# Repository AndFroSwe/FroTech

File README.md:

# This repo will be empried and removed

# FroTech library
Contains electrical projects that are too small to be in their own repo.

## Projects
Here, projects are listed.

### BoostBoard (WIP)
Board that can be connected to 5V and boost output to 9V or 12V. Meant
to be used in USB powered low power applications.

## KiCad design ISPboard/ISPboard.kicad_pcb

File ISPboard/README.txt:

#####################################
# README for ISPboard               #
# ###################################
# Project description:
# Board for attaching DIP28 Atmel chips
# and program and debug them over ISP.
# Also features 2 LEDs and 2 buttons that
# can be connected via jumpers to quickly test
# chip programming.
#####################################
# Revisions                         #
#####################################
Mk I
LEDS and buttons, connection for ISP.

Mk II
Added a PSU from battery and an on/off-switch.
Added pullups to buttons.

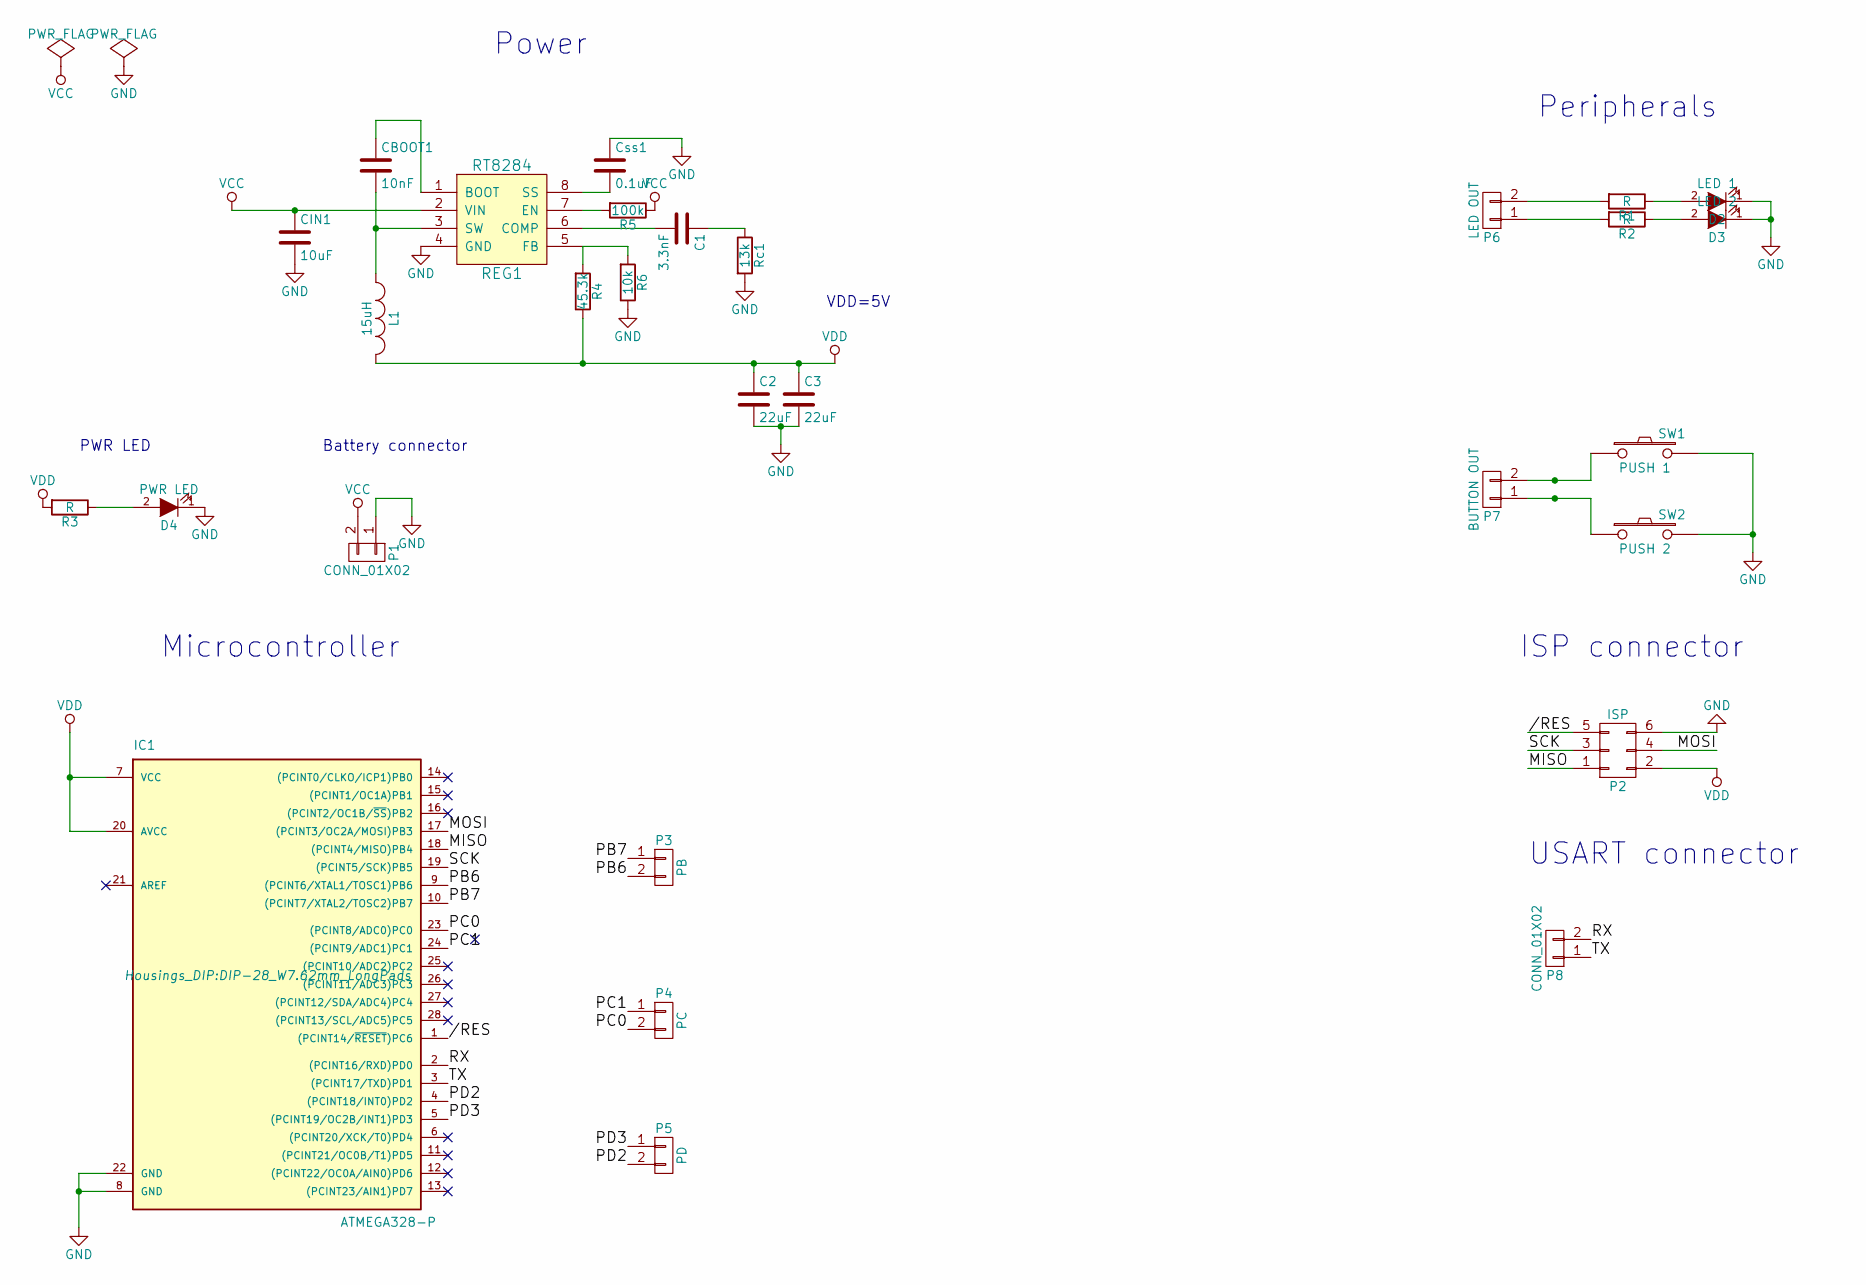
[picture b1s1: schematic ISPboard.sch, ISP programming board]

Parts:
C1: 3.3nF; C_0805_HandSoldering
C2, C3: 22uF; c_elec_4x4.5
CBOOT1: 10nF; C_0805_HandSoldering
CIN1: 10uF; c_elec_4x4.5
Css1: 0.1uF; C_0805_HandSoldering
D2: LED 1; LED-5MM
D3: LED 2; LED-5MM
D4: PWR LED; LED-5MM
IC1: ATMEGA328-P; DIP-28_W7.62mm_LongPads
L1: 15uH; Choke_SMD_Wuerth-WE-PD2-Typ-L
P1: CONN_01X02; Socket_Strip_Straight_1x02
P2: ISP; Socket_Strip_Straight_2x03
P3: PB; Molex_KK-6410-02_02x2.54mm_Straight
P4: PC; Molex_KK-6410-02_02x2.54mm_Straight
P5: PD; Molex_KK-6410-02_02x2.54mm_Straight
P6: LED OUT; Molex_KK-6410-02_02x2.54mm_Straight
P7: BUTTON OUT; Molex_KK-6410-02_02x2.54mm_Straight
P8: CONN_01X02; Molex_KK-6410-02_02x2.54mm_Straight
R1, R2, R3: R; R_1206_HandSoldering
R4: 45.3k; R_1206_HandSoldering
R5: 100k; R_1206_HandSoldering
R6: 10k; R_1206_HandSoldering
REG1: RT8284; SO-8
Rc1: 13k; R_1206_HandSoldering
SW1: PUSH 1; SW_PUSH_6mm
SW2: PUSH 2; SW_PUSH_6mm

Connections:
//RES: IC1.1 ((PCINT14/~RESET~)PC6), P2.5
/MISO: IC1.18 ((PCINT4/MISO)PB4), P2.1
/MOSI: IC1.17 ((PCINT3/OC2A/MOSI)PB3), P2.4
/PB6: IC1.9 ((PCINT6/XTAL1/TOSC1)PB6), P3.2
/PB7: IC1.10 ((PCINT7/XTAL2/TOSC2)PB7), P3.1
/PC0: IC1.23 ((PCINT8/ADC0)PC0), P4.2
/PC1: IC1.24 ((PCINT9/ADC1)PC1), P4.1
/PD2: IC1.4 ((PCINT18/INT0)PD2), P5.2
/PD3: IC1.5 ((PCINT19/OC2B/INT1)PD3), P5.1
/RX: IC1.2 ((PCINT16/RXD)PD0), P8.2
/SCK: IC1.19 ((PCINT5/SCK)PB5), P2.3
/TX: IC1.3 ((PCINT17/TXD)PD1), P8.1
GND: C2.2, C3.2, CIN1.2, Css1.1, D2.1 (K), D3.1 (K), D4.1 (K), IC1.8 (GND), IC1.22 (GND), P1.1, P2.6, R6.1, REG1.4 (GND), Rc1.2, SW1.2, SW2.2
unnamed: C1.1, Rc1.1
unnamed: C1.2, REG1.6 (COMP)
unnamed: CBOOT1.1, REG1.1 (BOOT)
unnamed: CBOOT1.2, L1.1, REG1.3 (SW)
unnamed: Css1.2, REG1.8 (SS)
unnamed: D2.2 (A), R1.1
unnamed: D3.2 (A), R2.1
unnamed: D4.2 (A), R3.1
unnamed: P6.1, R2.2
unnamed: P6.2, R1.2
unnamed: P7.1, SW2.1
unnamed: P7.2, SW1.1
unnamed: R4.2, R6.2, REG1.5 (FB)
unnamed: R5.2, REG1.7 (EN)
VCC: CIN1.1, P1.2, R5.1, REG1.2 (VIN)
VDD: C2.1, C3.1, IC1.7 (VCC), IC1.20 (AVCC), L1.2, P2.2, R3.2, R4.1

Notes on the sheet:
Microcontroller
Power
ISP connector
Peripherals
PWR LED
Battery connector
VDD=5V
USART connector

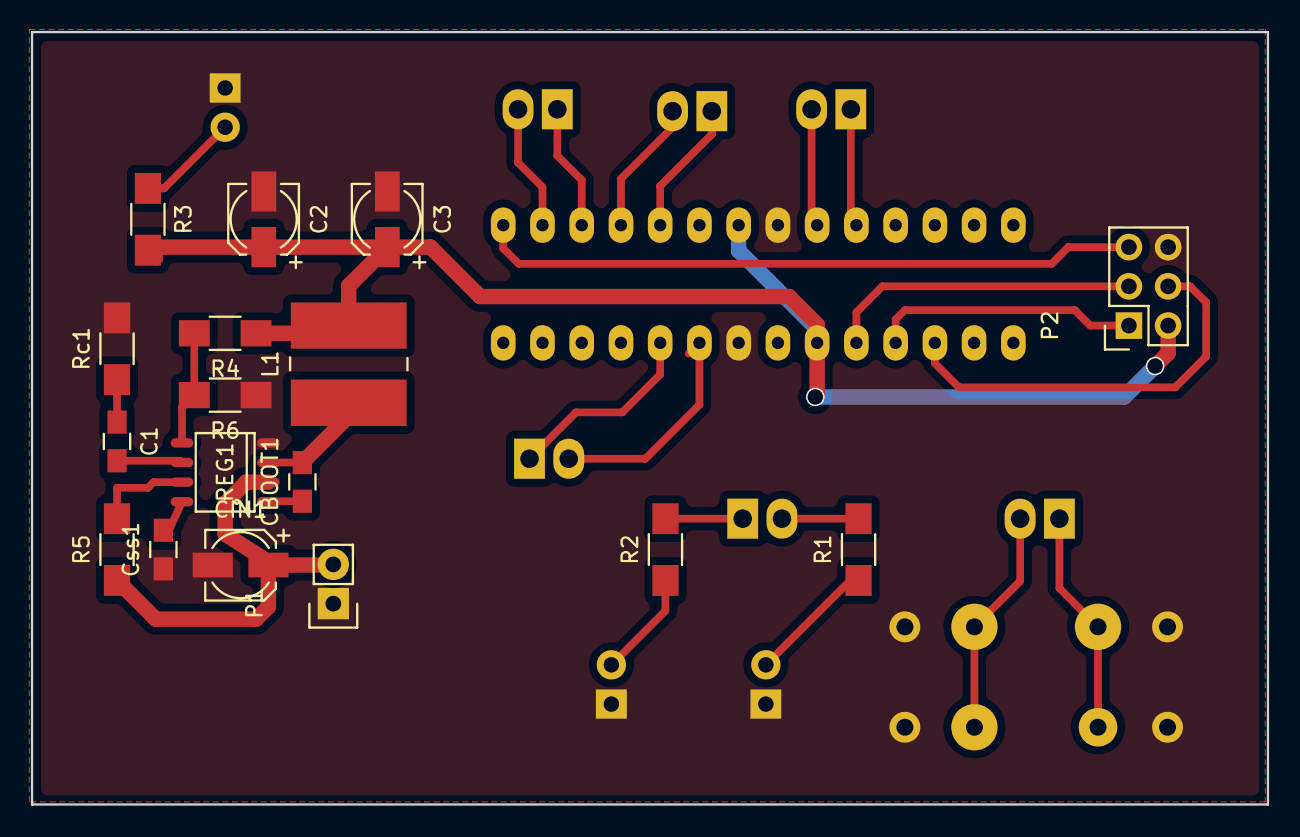
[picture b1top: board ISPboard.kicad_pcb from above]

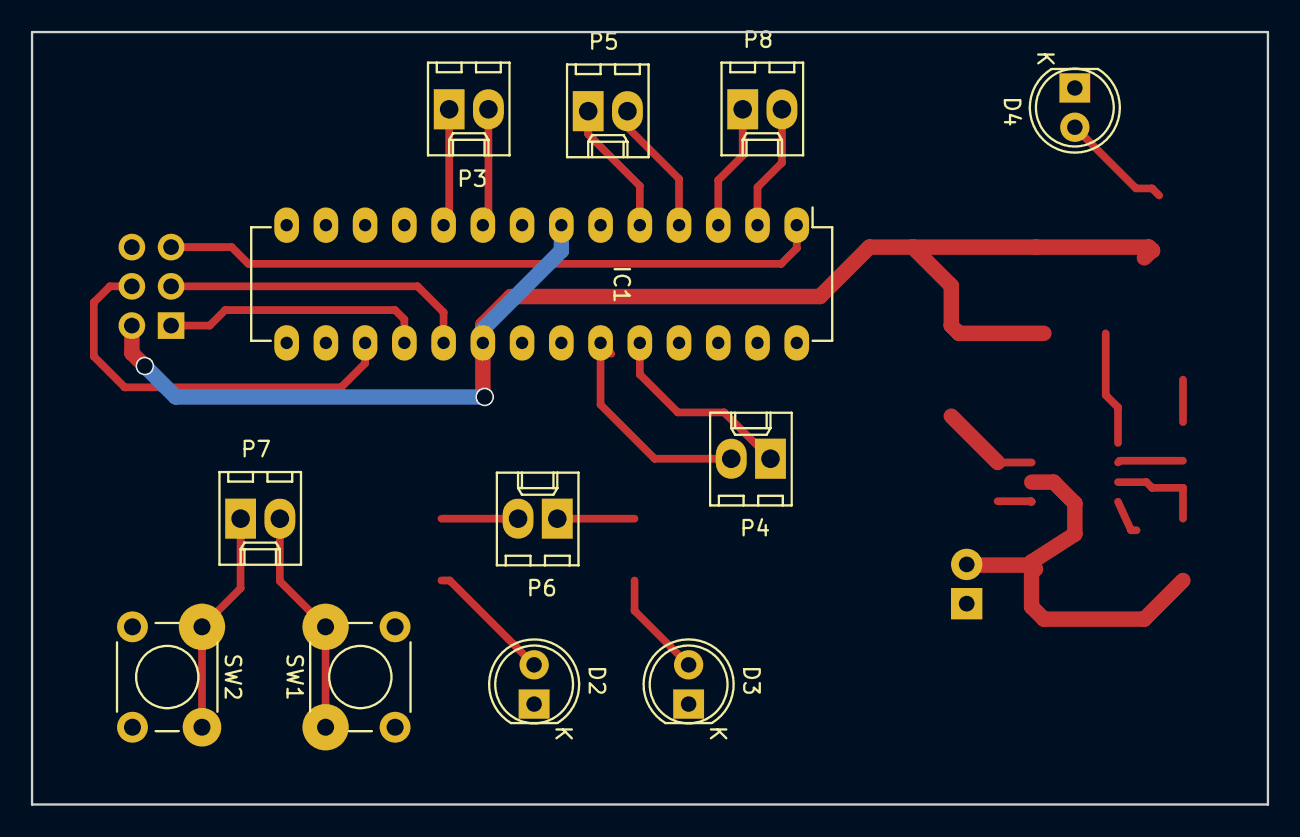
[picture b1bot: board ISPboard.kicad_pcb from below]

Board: 2 copper layers, 80.0 x 50.0 mm, 29 parts (12 on the bottom side), 29 nets.

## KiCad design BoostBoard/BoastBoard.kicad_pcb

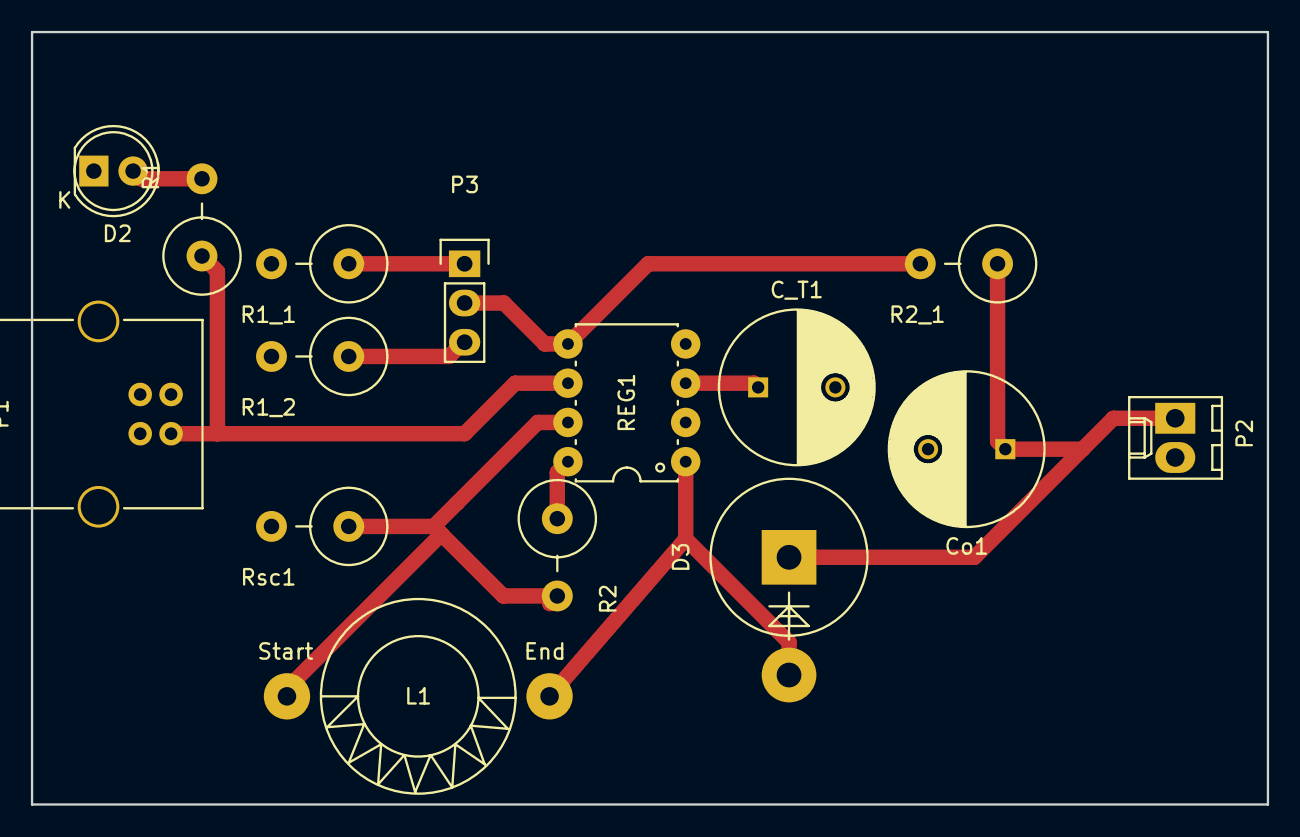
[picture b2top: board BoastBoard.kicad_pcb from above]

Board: 2 copper layers, 80.0 x 50.0 mm, 15 parts (0 on the bottom side), 11 nets.

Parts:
C_T1: 330uF; C_Radial_D10_L13_P5
Co1: 47uF; C_Radial_D10_L13_P5
D2: PWR_LED; LED-5MM
D3: D_Schottky_Small; Diode_P600_Vertical_AnodeUp
L1: 18uH; Choke_Toroid_horizontal_Diameter12-5mm_Amidon-T44
P1: USB_B
P2: CONN_01X02; Molex_KK-6410-02_02x2.54mm_Straight
P3: CONN_01X03; Pin_Header_Straight_1x03
R1: R220; Resistor_Vertical_RM5mm
R1_1: 36k; Resistor_Vertical_RM5mm
R1_2: 18k; Resistor_Vertical_RM5mm
R2: R180; Resistor_Vertical_RM5mm
R2_1: R; Resistor_Vertical_RM5mm
REG1: MC34063AP; PDIP-8
Rsc1: 0R15; Resistor_Vertical_RM5mm

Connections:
/DRIV_COL: R2.1, REG1.8
/INV_IN: P3.2, R2_1.2, REG1.5
/Ipk: L1.1, R2.2, REG1.7, Rsc1.1
/SW_COL: D3.2, L1.2, REG1.1
/TIM_CAP: C_T1.1, REG1.3
/Vout: Co1.1, D3.1, P2.1, R2_1.1
GND: C_T1.2, Co1.2, D2.1, P1.4, P2.2, R1_1.2, R1_2.2, REG1.2, REG1.4
unnamed: D2.2, R1.2
unnamed: P3.1, R1_1.1
unnamed: P3.3, R1_2.1
VCC: P1.1, R1.1, REG1.6, Rsc1.2

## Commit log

2016-11-27 Initial commit. Added readme and gitignore. Added ISPboard project from previous project. Started working on Boostboard
2016-12-10 Added the avr alarm project
2016-12-13 Made more work on the boostboard>
2016-12-13 Got display working on AVRAlarm
2016-12-14 Addded todo-list
2016-12-14 Added button interrupt with a counter on the display
2017-01-10 Fine tuned ispboard v2.
2017-01-11 Removed ISPBoard from repo to its own
